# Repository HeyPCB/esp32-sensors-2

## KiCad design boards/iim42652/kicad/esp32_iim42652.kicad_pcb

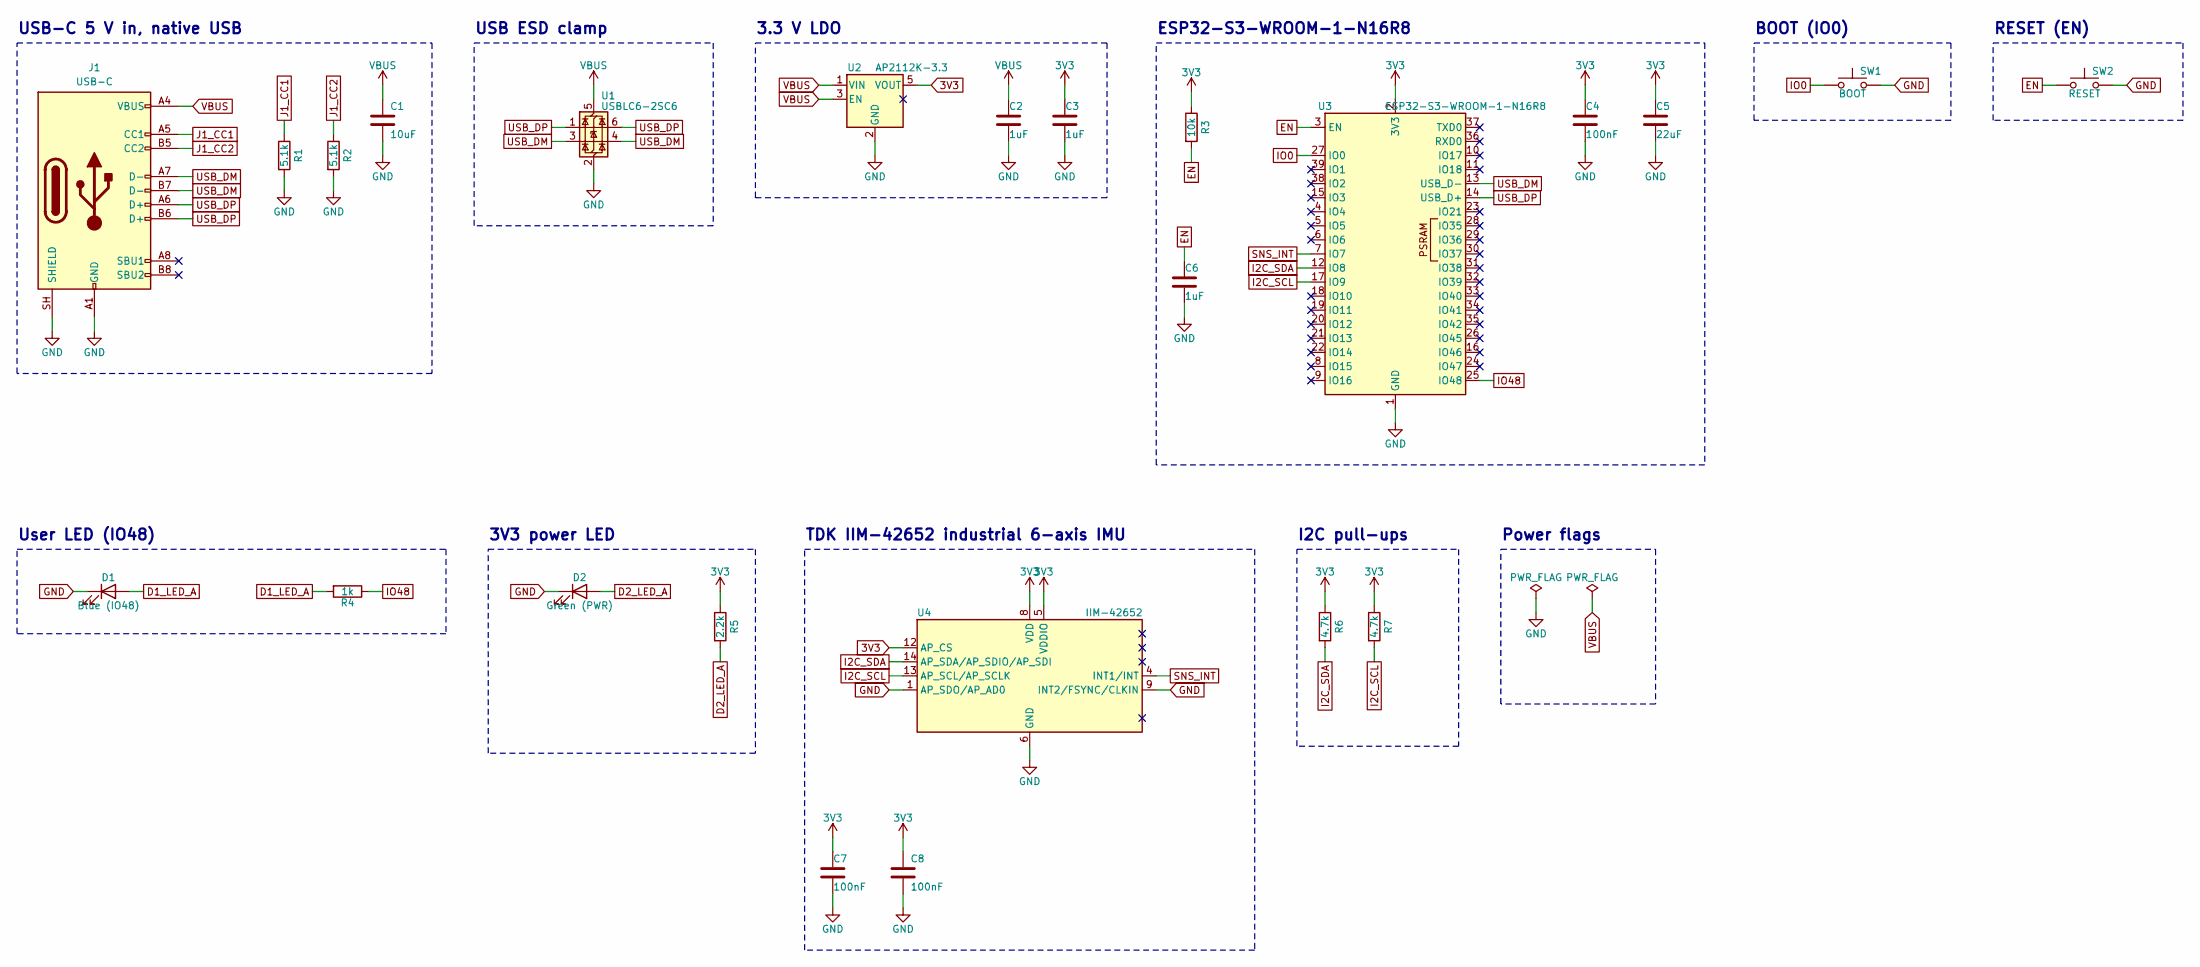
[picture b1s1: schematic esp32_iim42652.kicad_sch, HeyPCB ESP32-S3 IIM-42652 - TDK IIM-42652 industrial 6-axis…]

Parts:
C1: 10uF; C_0805_2012Metric; MPN CL21A106KAYNNNE; LCSC C15850
C2, C3, C6: 1uF; C_0603_1608Metric; MPN CL10A105KB8NNNC; LCSC C15849
C4: 100nF; C_0603_1608Metric; MPN CC0603KRX7R9BB104; LCSC C14663
C5: 22uF; C_0805_2012Metric; MPN CL21A226MAQNNNE; LCSC C45783
C7, C8: 100nF; C_0402_1005Metric; MPN CL05B104KO5NNNC; LCSC C1525
D1: Blue (IO48); LED_0603_1608Metric; MPN NCD0603B1; LCSC C84266
D2: Green (PWR); LED_0603_1608Metric; MPN KT-0603G; LCSC C12624
J1: USB-C; USB_C_Receptacle_HRO_TYPE-C-31-M-12; MPN TYPE-C-31-M-12; LCSC C165948
R1, R2: 5.1k; R_0402_1005Metric; MPN 0402WGF5101TCE; LCSC C25905
R3: 10k; R_0603_1608Metric; MPN 0603WAF1002T5E; LCSC C25804
R4: 1k; R_0603_1608Metric; MPN 0603WAF1001T5E; LCSC C21190
R5: 2.2k; R_0603_1608Metric; MPN 0603WAF2201T5E; LCSC C4190
R6, R7: 4.7k; R_0603_1608Metric; MPN 0603WAF4701T5E; LCSC C23162
SW1: BOOT; SW_Push_1P1T_XKB_TS-1187A; MPN TS-1187A-B-A-B; LCSC C318884
SW2: RESET; SW_Push_1P1T_XKB_TS-1187A; MPN TS-1187A-B-A-B; LCSC C318884
U1: USBLC6-2SC6; SOT-23-6; MPN USBLC6-2SC6; LCSC C7519
U2: AP2112K-3.3; SOT-23-5; MPN AP2112K-3.3TRG1; LCSC C51118
U3: ESP32-S3-WROOM-1-N16R8; ESP32-S3-WROOM-1; MPN ESP32-S3-WROOM-1-N16R8; LCSC C2913202
U4: IIM-42652; Bosch_LGA-14_3x2.5mm_P0.5mm; MPN IIM-42652; LCSC C2988404

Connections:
3V3: C3.1, C4.1, C5.1, C7.1, C8.1, R3.1, R5.1, R6.1, R7.1, U2.5 (VOUT), U3.2 (3V3), U4.5 (VDDIO), U4.8 (VDD), U4.12 (AP_CS)
D1_LED_A: D1.2 (A), R4.2
D2_LED_A: D2.2 (A), R5.2
EN: C6.1, R3.2, SW2.1, U3.3 (EN)
GND: C1.2, C2.2, C3.2, C4.2, C5.2, C6.2, C7.2, C8.2, D1.1 (K), D2.1 (K), J1.A1 (GND), J1.A12 (GND), J1.B1 (GND), J1.B12 (GND), J1.SH (SHIELD), R1.2, R2.2, SW1.2, SW2.2, U1.2 (GND), U2.2 (GND), U3.1 (GND), U3.40 (GND), U3.41 (GND), U4.1 (AP_SDO/AP_AD0), U4.6 (GND), U4.7 (GND), U4.9 (INT2/FSYNC/CLKIN)
I2C_SCL: R7.2, U3.17 (IO9), U4.13 (AP_SCL/AP_SCLK)
I2C_SDA: R6.2, U3.12 (IO8), U4.14 (AP_SDA/AP_SDIO/AP_SDI)
IO0: SW1.1, U3.27 (IO0)
IO48: R4.1, U3.25 (IO48)
J1_CC1: J1.A5 (CC1), R1.1
J1_CC2: J1.B5 (CC2), R2.1
SNS_INT: U3.7 (IO7), U4.4 (INT1/INT)
USB_DM: J1.A7 (D-), J1.B7 (D-), U1.3 (I/O2), U1.4 (I/O2), U3.13 (USB_D-)
USB_DP: J1.A6 (D+), J1.B6 (D+), U1.1 (I/O1), U1.6 (I/O1), U3.14 (USB_D+)
VBUS: C1.1, C2.1, J1.A4 (VBUS), J1.A9 (VBUS), J1.B4 (VBUS), J1.B9 (VBUS), U1.5 (VBUS), U2.1 (VIN), U2.3 (EN)

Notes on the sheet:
USB-C 5 V in, native USB
USB ESD clamp
3.3 V LDO
ESP32-S3-WROOM-1-N16R8
BOOT (IO0)
RESET (EN)
User LED (IO48)
3V3 power LED
TDK IIM-42652 industrial 6-axis IMU
I2C pull-ups
Power flags

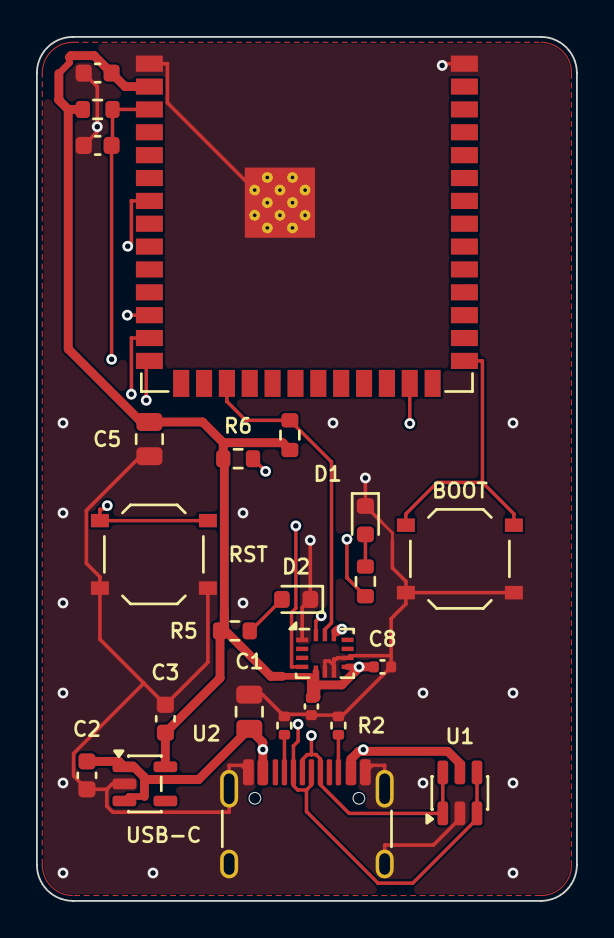
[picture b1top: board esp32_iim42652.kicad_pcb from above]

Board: 4 copper layers, 30.0 x 48.0 mm, 24 parts (0 on the bottom side), 15 nets.

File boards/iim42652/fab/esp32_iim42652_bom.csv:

"Reference","Value","Footprint","MPN","LCSC","Qty"
"C1","10uF","Capacitor_SMD:C_0805_2012Metric","CL21A106KAYNNNE","C15850","1"
"C2,C3,C6","1uF","Capacitor_SMD:C_0603_1608Metric","CL10A105KB8NNNC","C15849","3"
"C4","100nF","Capacitor_SMD:C_0603_1608Metric","CC0603KRX7R9BB104","C14663","1"
"C5","22uF","Capacitor_SMD:C_0805_2012Metric","CL21A226MAQNNNE","C45783","1"
"C7,C8","100nF","Capacitor_SMD:C_0402_1005Metric","CL05B104KO5NNNC","C1525","2"
"D1","Blue (IO48)","LED_SMD:LED_0603_1608Metric","NCD0603B1","C84266","1"
"D2","Green (PWR)","LED_SMD:LED_0603_1608Metric","KT-0603G","C12624","1"
"J1","USB-C","Connector_USB:USB_C_Receptacle_HRO_TYPE-C-31-M-12","TYPE-C-31-M-12","C165948","1"
"R1,R2","5.1k","Resistor_SMD:R_0402_1005Metric","0402WGF5101TCE","C25905","2"
"R3","10k","Resistor_SMD:R_0603_1608Metric","0603WAF1002T5E","C25804","1"
"R4","1k","Resistor_SMD:R_0603_1608Metric","0603WAF1001T5E","C21190","1"
"R5","2.2k","Resistor_SMD:R_0603_1608Metric","0603WAF2201T5E","C4190","1"
"R6,R7","4.7k","Resistor_SMD:R_0603_1608Metric","0603WAF4701T5E","C23162","2"
"SW1","BOOT","Button_Switch_SMD:SW_Push_1P1T_XKB_TS-1187A","TS-1187A-B-A-B","C318884","1"
"SW2","RESET","Button_Switch_SMD:SW_Push_1P1T_XKB_TS-1187A","TS-1187A-B-A-B","C318884","1"
"U1","USBLC6-2SC6","Package_TO_SOT_SMD:SOT-23-6","USBLC6-2SC6","C7519","1"
"U2","AP2112K-3.3","Package_TO_SOT_SMD:SOT-23-5","AP2112K-3.3TRG1","C51118","1"
"U3","ESP32-S3-WROOM-1-N16R8","RF_Module:ESP32-S3-WROOM-1","ESP32-S3-WROOM-1-N16R8","C2913202","1"
"U4","IIM-42652","Package_LGA:Bosch_LGA-14_3x2.5mm_P0.5mm","IIM-42652","C2988404","1"
